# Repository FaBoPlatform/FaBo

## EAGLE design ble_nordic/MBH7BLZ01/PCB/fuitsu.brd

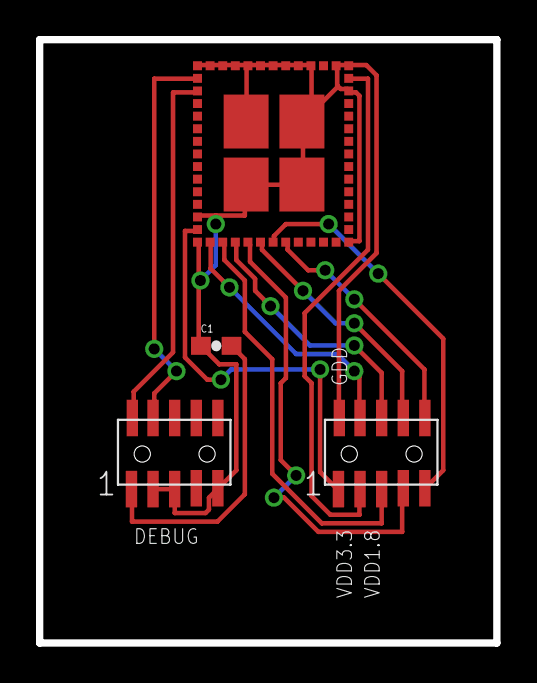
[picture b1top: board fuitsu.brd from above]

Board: 2 copper layers, 25.4 x 33.5 mm, 4 parts (0 on the bottom side), 13 nets.

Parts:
C1: 10μ; 0603-CAP
U$1: FUJITSU-MBH7BLZ02
U$2, U$3: PIN-HEADER-SMT(1.27MM)2X5

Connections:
3.3V: C1.2, U$2.1
GND: C1.1, U$1.1, U$1.3, U$1.15, U$1.27, U$1.29, U$1.41, U$1.42, U$1.43, U$1.44, U$1.45, U$1.46, U$1.47, U$1.48, U$1.49, U$1.50, U$1.52, U$1.53, U$1.54, U$1.55, U$1.56, U$2.3, U$2.5, U$2.9, U$3.2
GPIO_0: U$1.26, U$3.4
GPIO_1: U$1.25, U$3.5
GPIO_2: U$1.24, U$3.6
GPIO_3: U$1.23, U$3.7
GPIO_4: U$1.22, U$3.8
GPIO_5: U$1.21, U$3.9
GPIO_6: U$1.20, U$3.10
SWDCLK: U$1.40, U$2.4
SWDIO: U$1.39, U$2.2
VDD: U$1.28, U$3.1
VDD1.8: U$1.2, U$3.3

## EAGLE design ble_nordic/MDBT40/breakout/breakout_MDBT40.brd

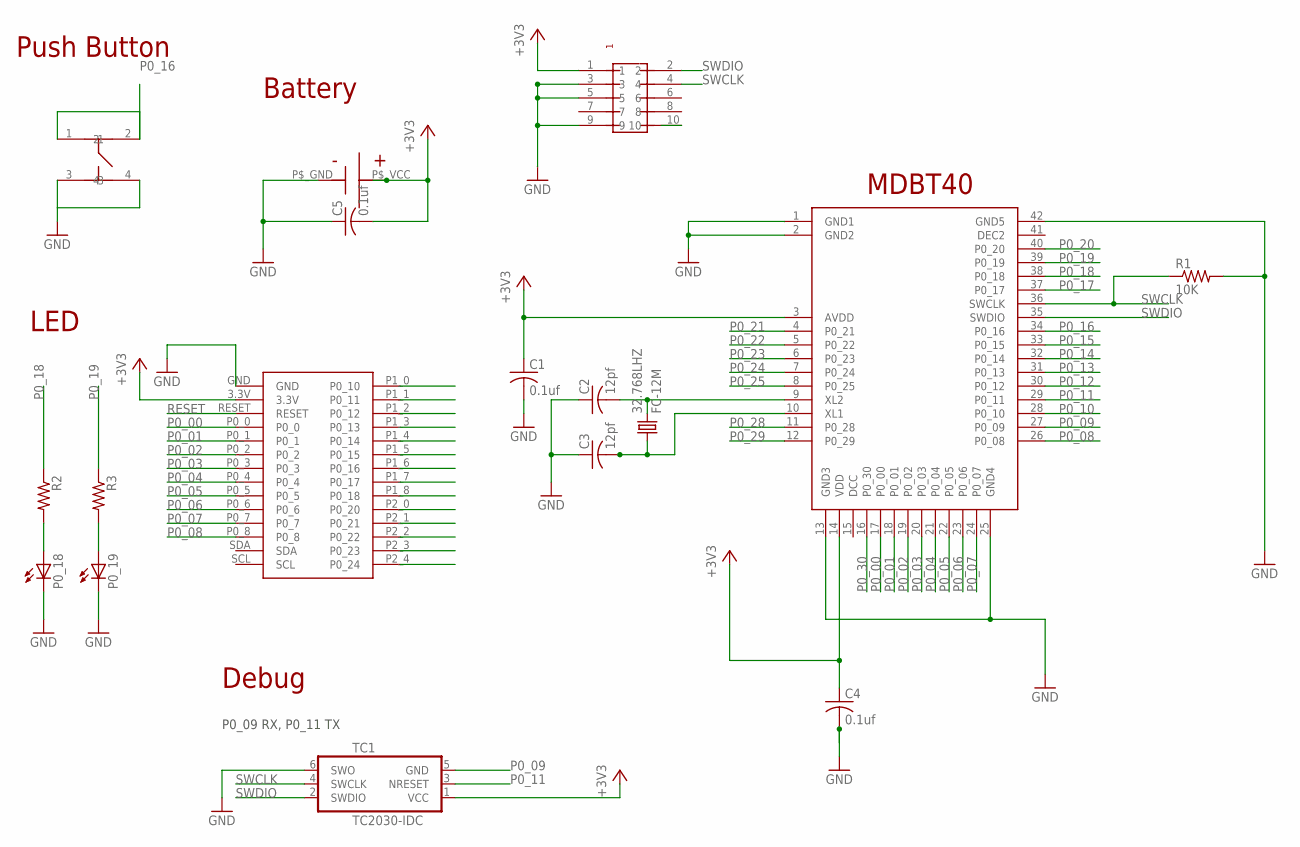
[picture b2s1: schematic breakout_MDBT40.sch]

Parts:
32.768LHZ: FC-12M
C1, C4, C5: 0.1uf; C0603
C2, C3: 12pf; C0603
P0_18, P0_19: LEDCHIP-LED0603; CHIP-LED0603
R1: 10K; R0603
R2, R3: R-US_R0603; R0603
TC1: TC2030-IDC
U$1: RAYTAC-MDBT40
U$2: SMTU2450-TOP; SMTU2450
U$3: BREAKOUT_BLE_NORDIC
U$4: PIN-HEADER-SMT(1.27MM)2X5
U$5: SWICTH-4P(KMR2); SWITCH-4P(KMR2)

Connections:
+3V3: C1.1, C4.1, C5.2, TC1.1 (VCC), U$1.3 (AVDD), U$1.14 (VDD), U$2.P$_VCC (+), U$3.3.3V, U$4.1
GND: C1.2, C2.1, C3.1, C4.2, C5.1, P0_18.C, P0_19.C, R1.2, TC1.6 (SWO), U$1.1 (GND1), U$1.2 (GND2), U$1.13 (GND3), U$1.25 (GND4), U$1.42 (GND5), U$2.P$_GND (-), U$3.GND, U$4.3, U$4.5, U$4.9, U$5.3, U$5.4
unnamed: P0_18.A, R2.2
unnamed: P0_19.A, R3.2
unnamed: 32.768LHZ.2, C2.2, U$1.9 (XL2)
unnamed: 32.768LHZ.1, C3.2, U$1.10 (XL1)
P0_00: U$1.17 (P0_00), U$3.P0_0
P0_01: U$1.18 (P0_01), U$3.P0_1
P0_02: U$1.19 (P0_02), U$3.P0_2
P0_03: U$1.20 (P0_03), U$3.P0_3
P0_04: U$1.21 (P0_04), U$3.P0_4
P0_05: U$1.22 (P0_05), U$3.P0_5
P0_06: U$1.23 (P0_06), U$3.P0_6
P0_07: U$1.24 (P0_07), U$3.P0_7
P0_08: U$1.26 (P0_08), U$3.P0_8
P0_09: TC1.5 (GND), U$1.27 (P0_09)
P0_10: U$1.28 (P0_10), U$3.P1_0 (P0_10)
P0_11: TC1.3 (NRESET), U$1.29 (P0_11), U$3.P1_1 (P0_11)
P0_12: U$1.30 (P0_12), U$3.P1_2 (P0_12)
P0_13: U$1.31 (P0_13), U$3.P1_3 (P0_13)
P0_14: U$1.32 (P0_14), U$3.P1_4 (P0_14)
P0_15: U$1.33 (P0_15), U$3.P1_5 (P0_15)
P0_16: U$1.34 (P0_16), U$3.P1_6 (P0_16), U$5.1, U$5.2
P0_17: U$1.37 (P0_17), U$3.P1_7 (P0_17)
P0_18: R2.1, U$1.38 (P0_18), U$3.P1_8 (P0_18)
P0_19: R3.1, U$1.39 (P0_19)
P0_20: U$1.40 (P0_20), U$3.P2_0 (P0_20)
P0_21: U$1.4 (P0_21), U$3.P2_1 (P0_21)
P0_22: U$1.5 (P0_22), U$3.P2_2 (P0_22)
P0_23: U$1.6 (P0_23), U$3.P2_3 (P0_23)
P0_24: U$1.7 (P0_24), U$3.P2_4 (P0_24)
P0_25: U$1.8 (P0_25)
P0_28: U$1.11 (P0_28)
P0_29: U$1.12 (P0_29)
P0_30: U$1.16 (P0_30)
RESET: U$3.RESET
RESET1: U$4.10
SWCLK: R1.1, TC1.4 (SWCLK), U$1.36 (SWCLK), U$4.4
SWDIO: TC1.2 (SWDIO), U$1.35 (SWDIO), U$4.2

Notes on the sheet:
Battery
Push Button
MDBT40
LED
Debug
P0_09 RX, P0_11 TX

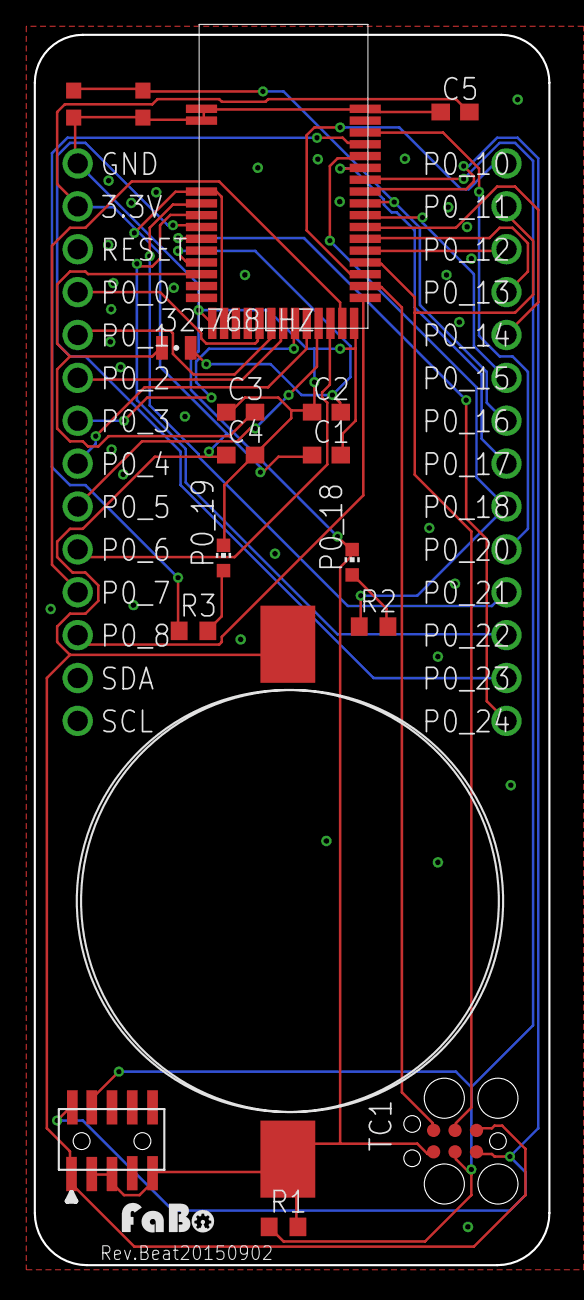
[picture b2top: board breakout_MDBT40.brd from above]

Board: 2 copper layers, 30.5 x 72.9 mm, 18 parts (0 on the bottom side), 33 nets.

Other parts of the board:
U$7: LOGO_FABO_S

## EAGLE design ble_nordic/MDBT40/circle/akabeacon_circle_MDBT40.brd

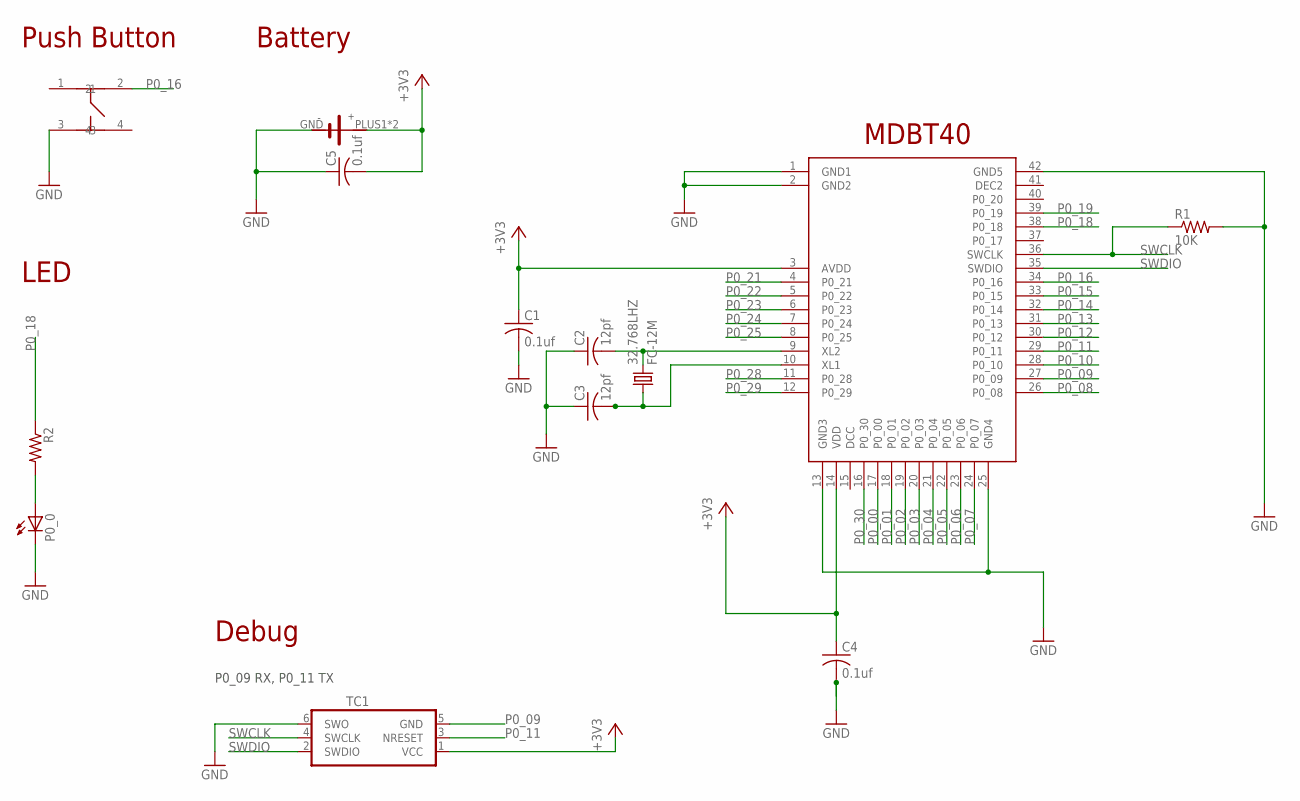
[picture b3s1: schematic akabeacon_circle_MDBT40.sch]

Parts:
32.768LHZ: FC-12M
C1, C4, C5: 0.1uf; C0603
C2, C3: 12pf; C0603
P0_0: LEDCHIP-LED0603; CHIP-LED0603
R1: 10K; R0603
R2: R-US_R0603; R0603
TC1: TC2030-IDC-NL
U$1: RAYTAC-MDBT40
U$5: SWICTH-4P(KMR2); SWITCH-4P(KMR2)
U$7: CIRCLE-TYPE1; CIRCLE-TYE1-TC2030

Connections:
+3V3: C1.1, C4.1, C5.2, TC1.1 (VCC), U$1.3 (AVDD), U$1.14 (VDD), U$7.PLUS1 (VCC), U$7.PLUS2 (VCC)
GND: C1.2, C2.1, C3.1, C4.2, C5.1, P0_0.C, R1.2, TC1.6 (SWO), U$1.1 (GND1), U$1.2 (GND2), U$1.13 (GND3), U$1.25 (GND4), U$1.42 (GND5), U$5.3, U$7.GND
unnamed: P0_0.A, R2.2
unnamed: 32.768LHZ.2, C2.2, U$1.9 (XL2)
unnamed: 32.768LHZ.1, C3.2, U$1.10 (XL1)
P0_00: U$1.17 (P0_00)
P0_01: U$1.18 (P0_01)
P0_02: U$1.19 (P0_02)
P0_03: U$1.20 (P0_03)
P0_04: U$1.21 (P0_04)
P0_05: U$1.22 (P0_05)
P0_06: U$1.23 (P0_06)
P0_07: U$1.24 (P0_07)
P0_08: U$1.26 (P0_08)
P0_09: TC1.5 (GND), U$1.27 (P0_09)
P0_10: U$1.28 (P0_10)
P0_11: TC1.3 (NRESET), U$1.29 (P0_11)
P0_12: U$1.30 (P0_12)
P0_13: U$1.31 (P0_13)
P0_14: U$1.32 (P0_14)
P0_15: U$1.33 (P0_15)
P0_16: U$1.34 (P0_16), U$5.2
P0_18: R2.1, U$1.38 (P0_18)
P0_19: U$1.39 (P0_19)
P0_21: U$1.4 (P0_21)
P0_22: U$1.5 (P0_22)
P0_23: U$1.6 (P0_23)
P0_24: U$1.7 (P0_24)
P0_25: U$1.8 (P0_25)
P0_28: U$1.11 (P0_28)
P0_29: U$1.12 (P0_29)
P0_30: U$1.16 (P0_30)
SWCLK: R1.1, TC1.4 (SWCLK), U$1.36 (SWCLK)
SWDIO: TC1.2 (SWDIO), U$1.35 (SWDIO)

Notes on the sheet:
Battery
Push Button
MDBT40
LED
Debug
P0_09 RX, P0_11 TX

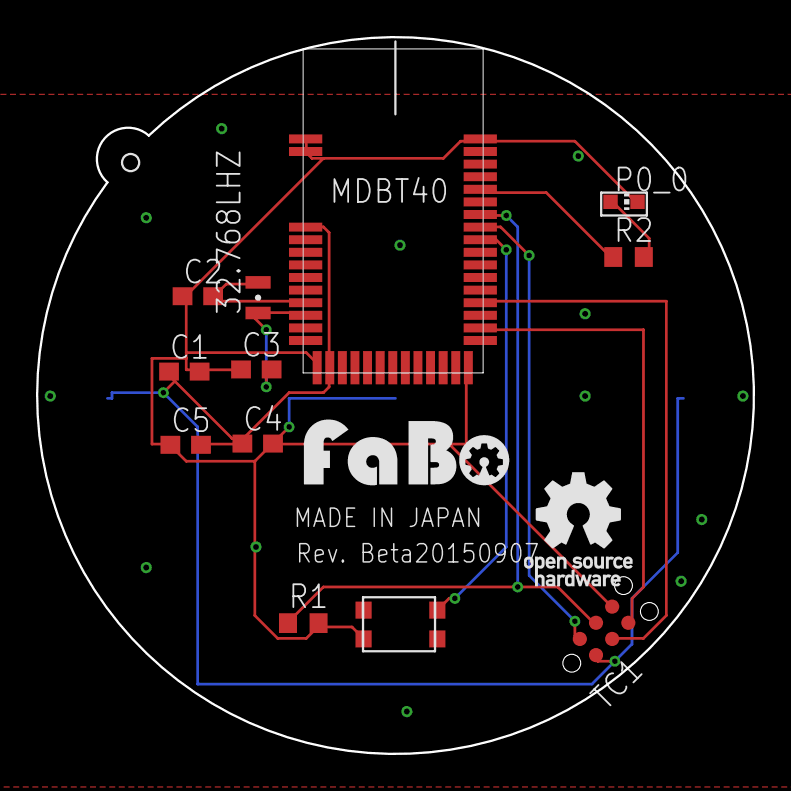
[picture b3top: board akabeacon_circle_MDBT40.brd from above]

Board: 2 copper layers, 39.8 x 39.8 mm, 15 parts (0 on the bottom side), 11 nets.

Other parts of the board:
U$2: LOGO_FABO_M
U$4: LOGO_OSHW_T_M

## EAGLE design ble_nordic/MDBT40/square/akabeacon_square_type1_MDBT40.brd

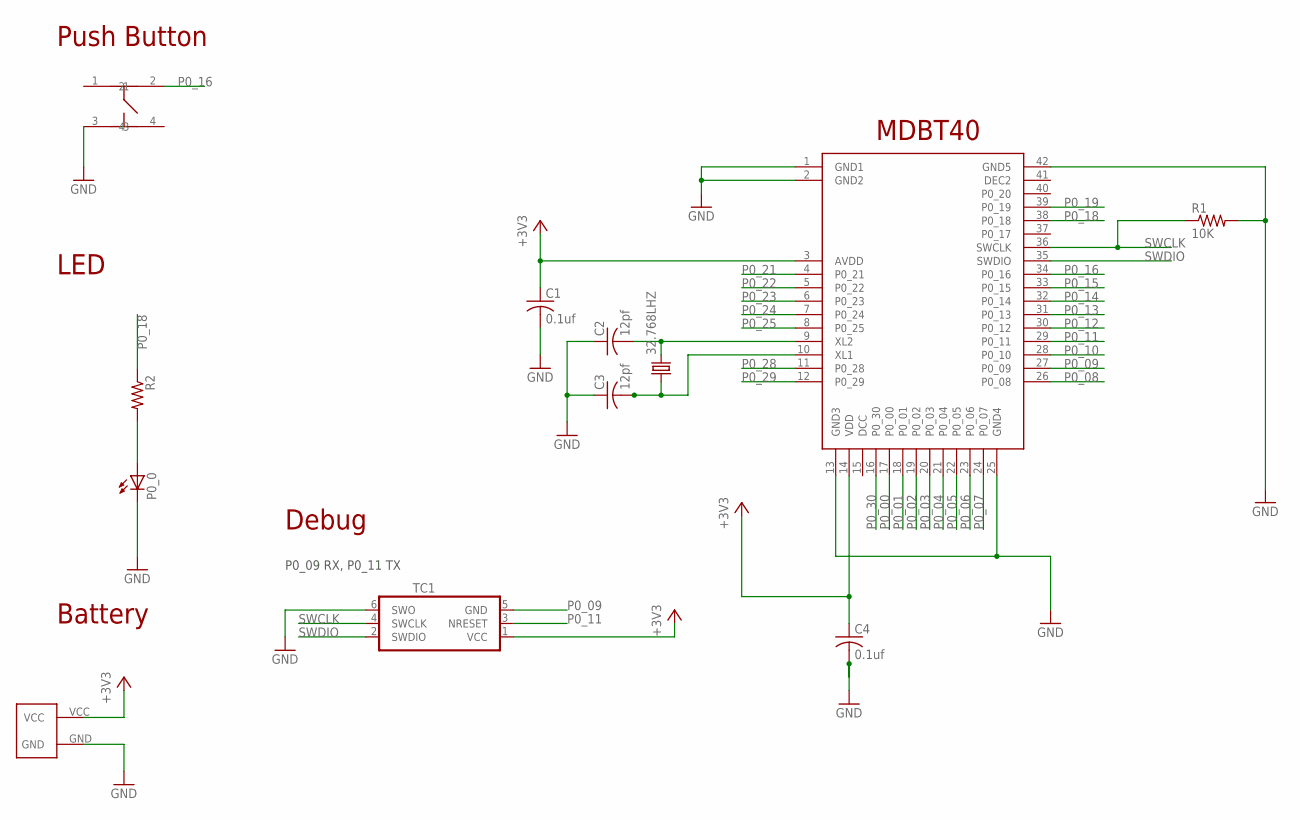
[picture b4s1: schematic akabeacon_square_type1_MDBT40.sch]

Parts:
32.768LHZ: FC-12M
C1, C4: 0.1uf; C0603
C2, C3: 12pf; C0603
P0_0: LEDCHIP-LED0603; CHIP-LED0603
R1: 10K; R0603
R2: R-US_R0603; R0603
TC1: TC2030-IDC-NL
U$2: SQUARE-TYPE1; SQUARE-TYPE1-TC2030
U$3: RAYTAC-MDBT40
U$6: SWICTH-4P(KMR2); SWITCH-4P(KMR2)

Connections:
+3V3: C1.1, C4.1, TC1.1 (VCC), U$2.VCC, U$3.3 (AVDD), U$3.14 (VDD)
GND: C1.2, C2.1, C3.1, C4.2, P0_0.C, R1.2, TC1.6 (SWO), U$2.GND, U$3.1 (GND1), U$3.2 (GND2), U$3.13 (GND3), U$3.25 (GND4), U$3.42 (GND5), U$6.3
unnamed: P0_0.A, R2.2
unnamed: 32.768LHZ.2, C2.2, U$3.9 (XL2)
unnamed: 32.768LHZ.1, C3.2, U$3.10 (XL1)
P0_00: U$3.17 (P0_00)
P0_01: U$3.18 (P0_01)
P0_02: U$3.19 (P0_02)
P0_03: U$3.20 (P0_03)
P0_04: U$3.21 (P0_04)
P0_05: U$3.22 (P0_05)
P0_06: U$3.23 (P0_06)
P0_07: U$3.24 (P0_07)
P0_08: U$3.26 (P0_08)
P0_09: TC1.5 (GND), U$3.27 (P0_09)
P0_10: U$3.28 (P0_10)
P0_11: TC1.3 (NRESET), U$3.29 (P0_11)
P0_12: U$3.30 (P0_12)
P0_13: U$3.31 (P0_13)
P0_14: U$3.32 (P0_14)
P0_15: U$3.33 (P0_15)
P0_16: U$3.34 (P0_16), U$6.2
P0_18: R2.1, U$3.38 (P0_18)
P0_19: U$3.39 (P0_19)
P0_21: U$3.4 (P0_21)
P0_22: U$3.5 (P0_22)
P0_23: U$3.6 (P0_23)
P0_24: U$3.7 (P0_24)
P0_25: U$3.8 (P0_25)
P0_28: U$3.11 (P0_28)
P0_29: U$3.12 (P0_29)
P0_30: U$3.16 (P0_30)
SWCLK: R1.1, TC1.4 (SWCLK), U$3.36 (SWCLK)
SWDIO: TC1.2 (SWDIO), U$3.35 (SWDIO)

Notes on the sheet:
Battery
Push Button
Debug
MDBT40
LED
P0_09 RX, P0_11 TX

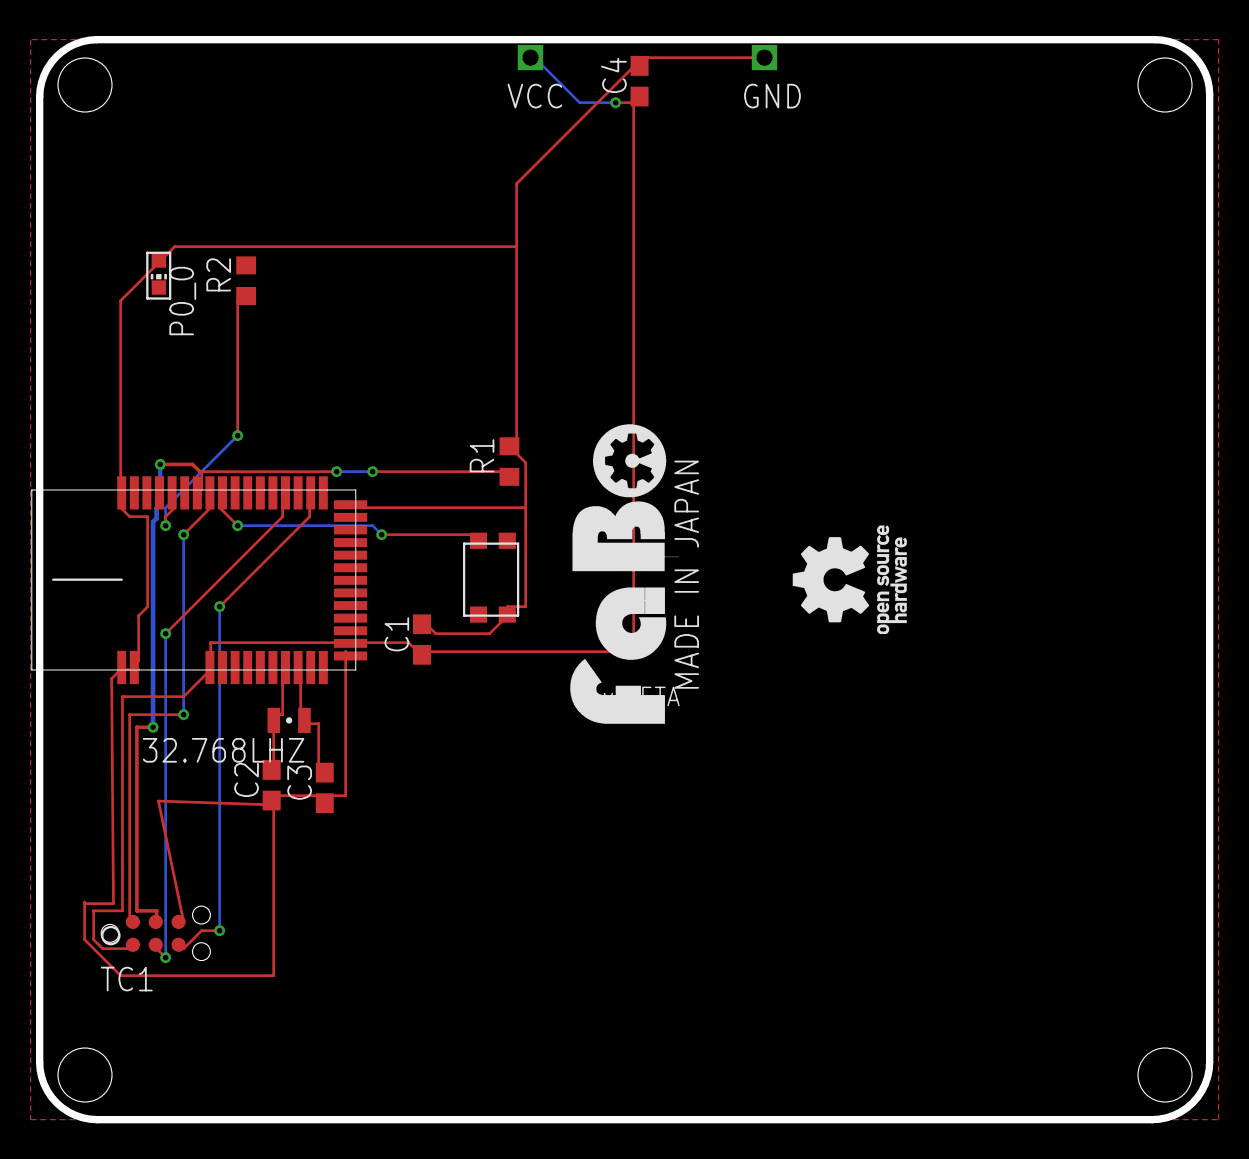
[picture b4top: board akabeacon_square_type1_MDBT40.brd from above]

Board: 2 copper layers, 65.0 x 60.0 mm, 12 parts (0 on the bottom side), 11 nets.

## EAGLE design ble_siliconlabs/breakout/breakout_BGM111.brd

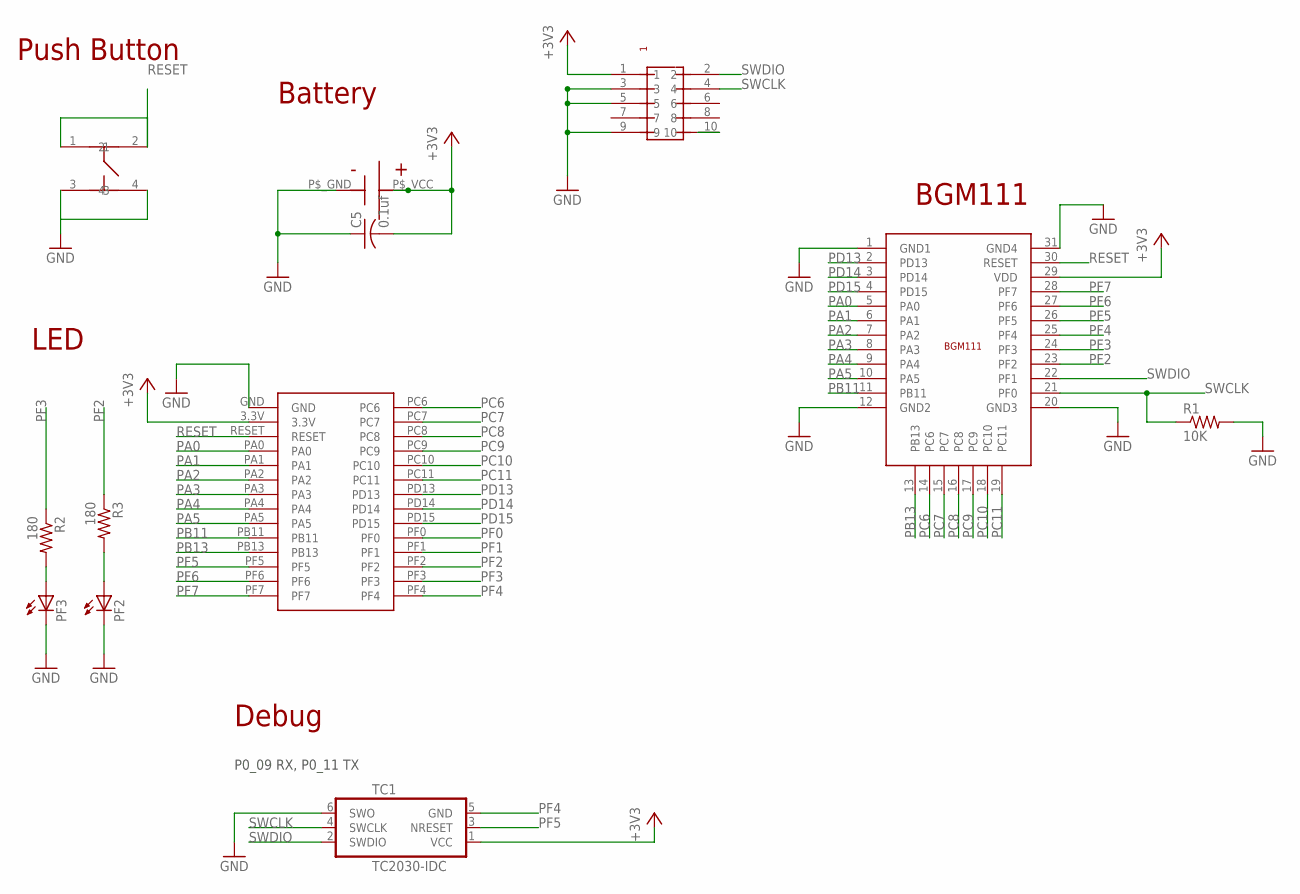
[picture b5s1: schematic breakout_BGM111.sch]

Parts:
C5: 0.1uf; C0603
PF2, PF3: LEDCHIP-LED0603; CHIP-LED0603
R1: 10K; R0603
R2, R3: 180; R0603
TC1: TC2030-IDC
U$1: SILICONLABS-BGM111
U$2: SMTU2450-TOP; SMTU2450
U$3: BLE-BREAKOUT-NORDIC; BLE-BREAKOUT-SILICONLABS
U$4: PIN-HEADER-SMT(1.27MM)2X5
U$5: SWICTH-4P(KMR2); SWITCH-4P(KMR2)

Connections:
+3V3: C5.2, TC1.1 (VCC), U$1.29 (VDD), U$2.P$_VCC (+), U$3.3.3V, U$4.1
GND: C5.1, PF2.C, PF3.C, R1.2, TC1.6 (SWO), U$1.1 (GND1), U$1.12 (GND2), U$1.20 (GND3), U$1.31 (GND4), U$2.P$_GND (-), U$3.GND, U$4.3, U$4.5, U$4.9, U$5.3, U$5.4
unnamed: PF3.A, R2.2
unnamed: PF2.A, R3.2
PA0: U$1.5 (PA0), U$3.PA0
PA1: U$1.6 (PA1), U$3.PA1
PA2: U$1.7 (PA2), U$3.PA2
PA3: U$1.8 (PA3), U$3.PA3
PA4: U$1.9 (PA4), U$3.PA4
PA5: U$1.10 (PA5), U$3.PA5
PB11: U$1.11 (PB11), U$3.PB11
PB13: U$1.13 (PB13), U$3.PB13
PC6: U$1.14 (PC6), U$3.PC6
PC7: U$1.15 (PC7), U$3.PC7
PC8: U$1.16 (PC8), U$3.PC8
PC9: U$1.17 (PC9), U$3.PC9
PC10: U$1.18 (PC10), U$3.PC10
PC11: U$1.19 (PC11), U$3.PC11
PD13: U$1.2 (PD13), U$3.PD13
PD14: U$1.3 (PD14), U$3.PD14
PD15: U$1.4 (PD15), U$3.PD15
PF0: U$3.PF0
PF1: U$3.PF1
PF2: R3.1, U$1.23 (PF2), U$3.PF2
PF3: R2.1, U$1.24 (PF3), U$3.PF3
PF4: TC1.5 (GND), U$1.25 (PF4), U$3.PF4
PF5: TC1.3 (NRESET), U$1.26 (PF5), U$3.PF5
PF6: U$1.27 (PF6), U$3.PF6
PF7: U$1.28 (PF7), U$3.PF7
RESET: U$1.30 (RESET), U$3.RESET, U$5.1, U$5.2
RESET1: U$4.10
SWCLK: R1.1, TC1.4 (SWCLK), U$1.21 (PF0), U$4.4
SWDIO: TC1.2 (SWDIO), U$1.22 (PF1), U$4.2

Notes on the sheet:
Battery
Push Button
BGM111
LED
Debug
P0_09 RX, P0_11 TX

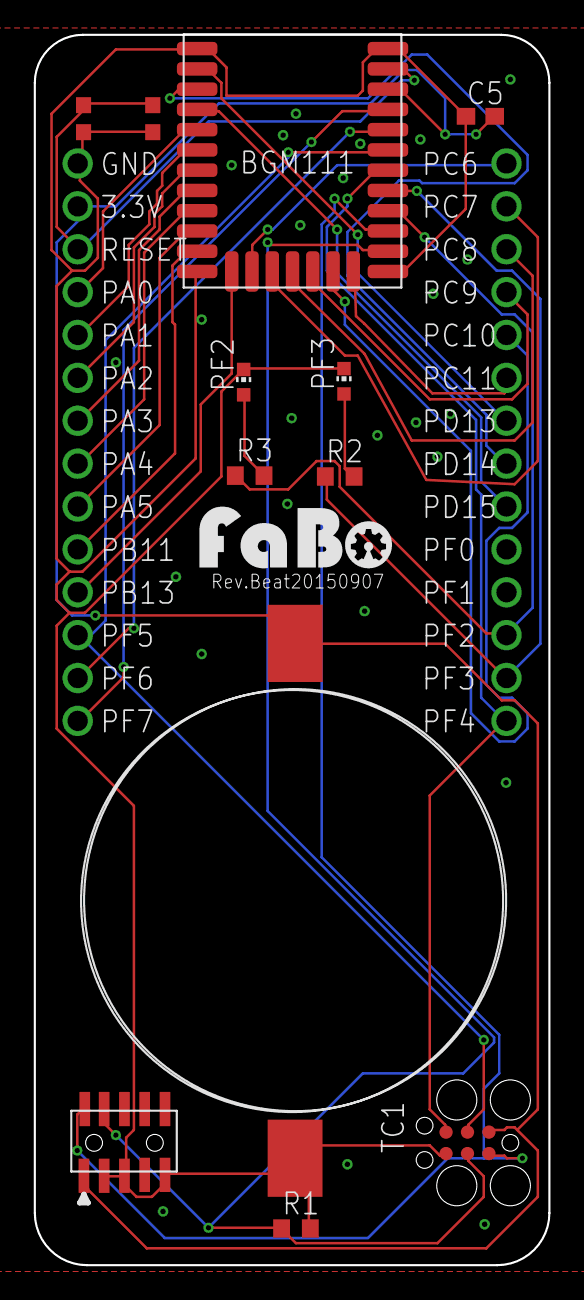
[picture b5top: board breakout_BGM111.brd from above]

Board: 2 copper layers, 30.5 x 72.9 mm, 13 parts (0 on the bottom side), 30 nets.

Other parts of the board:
U$7: LOGO_FABO_M

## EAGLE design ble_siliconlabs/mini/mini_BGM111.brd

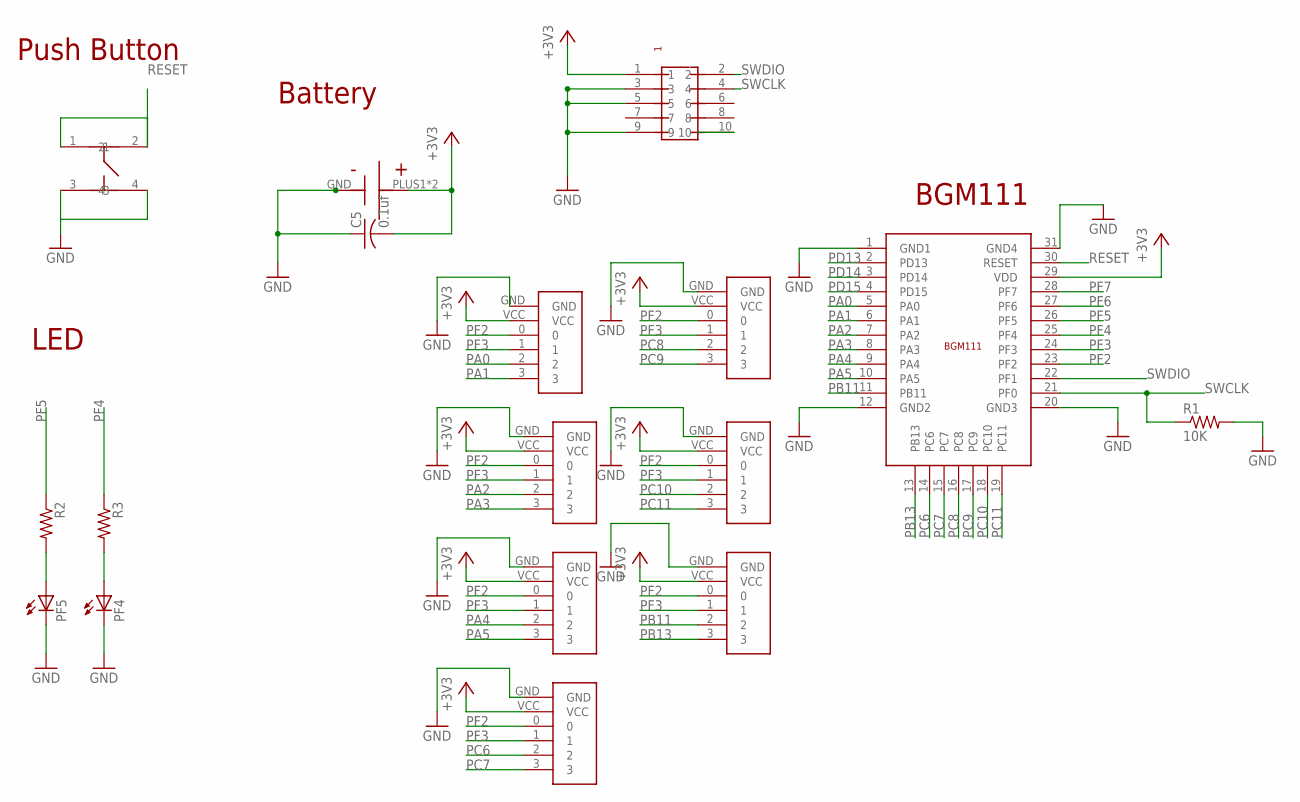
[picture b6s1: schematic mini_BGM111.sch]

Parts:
C5: 0.1uf; C0603
PF4, PF5: LEDCHIP-LED0603; CHIP-LED0603
R1: 10K; R0603
R2, R3: R-US_R0603; R0603
U$1: SILICONLABS-BGM111
U$2, U$3, U$7, U$8, U$9, U$10: FABO-PIN-HEADER-2X3-SMD
U$4: PIN-HEADER-SMT(1.27MM)2X5
U$5: SWICTH-4P(KMR2); SWITCH-4P(KMR2)
U$11: FABO-PIN-HEADER-2X3-SMD-BOTTOM
U$12: BRX1-2477

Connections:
+3V3: C5.2, U$1.29 (VDD), U$2.VCC, U$3.VCC, U$4.1, U$7.VCC, U$8.VCC, U$9.VCC, U$10.VCC, U$11.VCC, U$12.PLUS1 (+), U$12.PLUS2 (+)
GND: C5.1, PF4.C, PF5.C, R1.2, U$1.1 (GND1), U$1.12 (GND2), U$1.20 (GND3), U$1.31 (GND4), U$2.GND, U$3.GND, U$4.3, U$4.5, U$4.9, U$5.3, U$5.4, U$7.GND, U$8.GND, U$9.GND, U$10.GND, U$11.GND, U$12.GND (-)
unnamed: PF5.A, R2.2
unnamed: PF4.A, R3.2
PA0: U$1.5 (PA0), U$3.2
PA1: U$1.6 (PA1), U$3.3
PA2: U$1.7 (PA2), U$7.2
PA3: U$1.8 (PA3), U$7.3
PA4: U$1.9 (PA4), U$8.2
PA5: U$1.10 (PA5), U$8.3
PB11: U$1.11 (PB11), U$11.2
PB13: U$1.13 (PB13), U$11.3
PC6: U$1.14 (PC6), U$2.2
PC7: U$1.15 (PC7), U$2.3
PC8: U$1.16 (PC8), U$9.2
PC9: U$1.17 (PC9), U$9.3
PC10: U$1.18 (PC10), U$10.2
PC11: U$1.19 (PC11), U$10.3
PD13: U$1.2 (PD13)
PD14: U$1.3 (PD14)
PD15: U$1.4 (PD15)
PF2: U$1.23 (PF2), U$2.0, U$3.0, U$7.0, U$8.0, U$9.0, U$10.0, U$11.0
PF3: U$1.24 (PF3), U$2.1, U$3.1, U$7.1, U$8.1, U$9.1, U$10.1, U$11.1
PF4: R3.1, U$1.25 (PF4)
PF5: R2.1, U$1.26 (PF5)
PF6: U$1.27 (PF6)
PF7: U$1.28 (PF7)
RESET: U$1.30 (RESET), U$5.1, U$5.2
RESET1: U$4.10
SWCLK: R1.1, U$1.21 (PF0), U$4.4
SWDIO: U$1.22 (PF1), U$4.2

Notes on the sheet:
Battery
Push Button
BGM111
LED

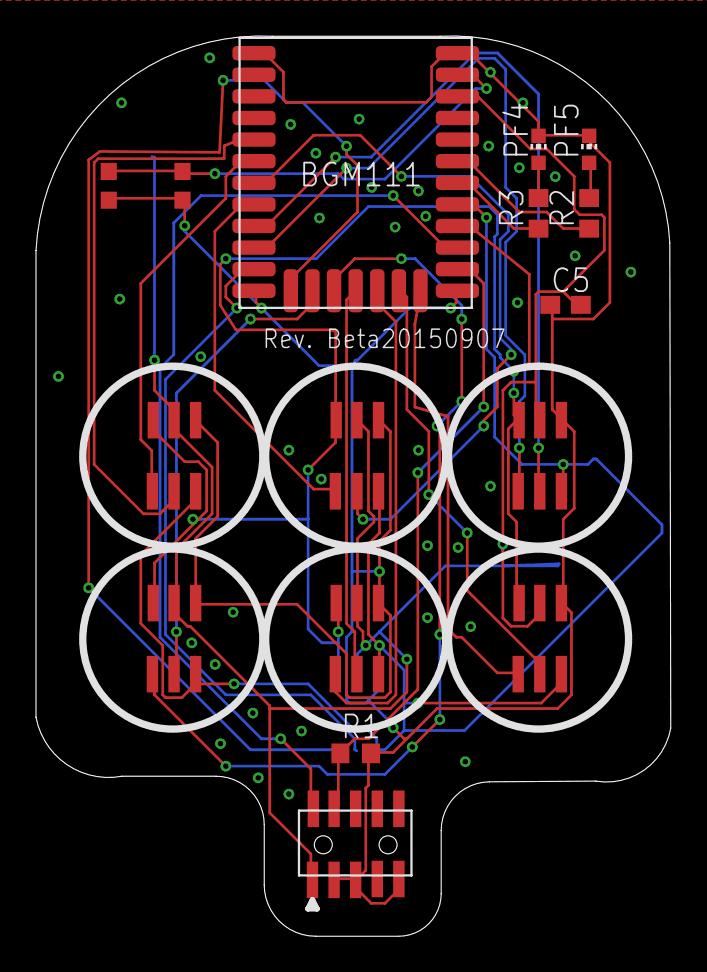
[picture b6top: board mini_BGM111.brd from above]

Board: 2 copper layers, 35.3 x 50.0 mm, 17 parts (0 on the bottom side), 25 nets.

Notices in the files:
parts and their libraries:
SparkFun: Licensing: CC v3.0 Share-Alike You are welcome to use this library for commercial purposes.
gclue: Released under the Creative Commons
gclue: https://creativecommons.org/licenses/by-sa/4.0
